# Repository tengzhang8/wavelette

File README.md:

wavelette
=========

wavelette.com

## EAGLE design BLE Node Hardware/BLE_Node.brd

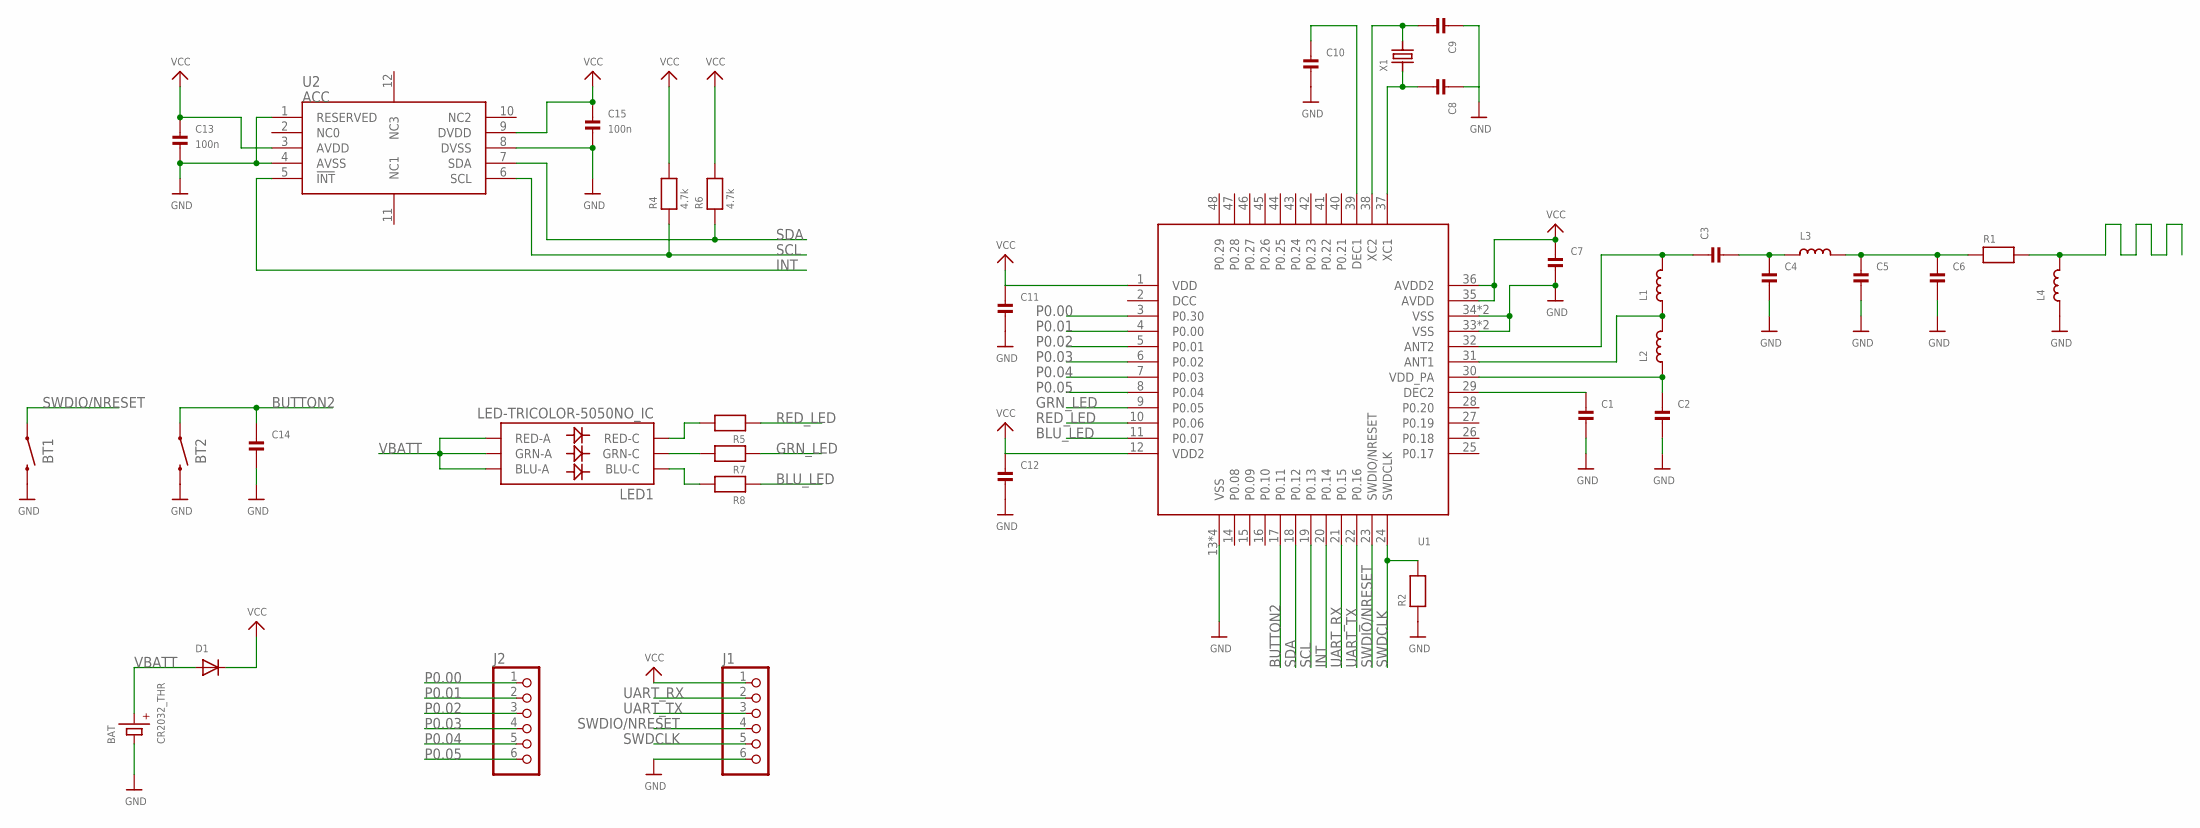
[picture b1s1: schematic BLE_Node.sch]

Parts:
BAT: CR2032_THR
BT1, BT2: TACT_SWITCH_3.5MM_6MM; TACT_SW_3.5MM_6MM
C1, C2, C3, C4, C5, C6, C7, C8, C9, C10, C11, C12, C14: NRF51_CAP_0402
C13, C15: 100n; NRF51_CAP_0402
D1: DIODESOT23_REFLOW; SOT23-R
J1, J2: HEADER-1X6ROUND; 1X06_ROUND
L1, L2, L3, L4: NRF51_IND_0402
LED1: LED-TRICOLOR-5050NO_IC; LED-TRICOLOR-5050
R1, R2, R5, R7, R8: NRF51_RES_0402
R4, R6: 4.7k; NRF51_RES_0402
U1: NRF51822_QFN48; NORDIC_QFN48
U2: ACC; DFN10
X1: TSX-3225_16MHZ; XTAL_3.2X2.5

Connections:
BLU_LED: R8.1, U1.11 (P0.07)
BUTTON2: BT2.1, C14.1, U1.17 (P0.11)
GND: BAT.5 (-), BT1.2, BT2.2, C1.2, C2.2, C4.2, C5.2, C6.2, C7.2, C8.1, C9.1, C10.2, C11.2, C12.2, C13.2, C14.2, C15.2, J1.6, L4.1, R2.1, U1.13 (VSS), U1.33 (VSS), U1.34 (VSS), U1.49 (VSS), U1.50 (VSS), U1.51 (VSS), U1.52 (VSS), U1.53 (VSS), U2.1 (RESERVED), U2.4 (AVSS), U2.8 (DVSS)
GRN_LED: R7.1, U1.9 (P0.05)
INT: U1.20 (P0.14), U2.5 (!INT)
unnamed: L1.1, L2.2, U1.31 (ANT1)
unnamed: C1.1, U1.29 (DEC2)
unnamed: C2.1, L2.1, U1.30 (VDD_PA)
unnamed: C3.1, L1.2, U1.32 (ANT2)
unnamed: C3.2, C4.1, L3.1
unnamed: C5.1, C6.1, L3.2, R1.1
unnamed: L4.2, R1.2
unnamed: C8.2, U1.37 (XC1), X1.1
unnamed: C9.2, U1.38 (XC2), X1.3 (2)
unnamed: C10.1, U1.39 (DEC1)
unnamed: LED1.5 (RED-C), R5.2
unnamed: LED1.6 (GRN-C), R7.2
unnamed: LED1.4 (BLU-C), R8.2
P0.00: J2.1, U1.3 (P0.30)
P0.01: J2.2, U1.4 (P0.00)
P0.02: J2.3, U1.5 (P0.01)
P0.03: J2.4, U1.6 (P0.02)
P0.04: J2.5, U1.7 (P0.03)
P0.05: J2.6, U1.8 (P0.04)
RED_LED: R5.1, U1.10 (P0.06)
SCL: R4.1, U1.19 (P0.13), U2.6 (SCL)
SDA: R6.1, U1.18 (P0.12), U2.7 (SDA)
SWDCLK: J1.5, R2.2, U1.24 (SWDCLK)
SWDIO/NRESET: BT1.1, J1.4, U1.23 (SWDIO/NRESET)
UART_RX: J1.2, U1.21 (P0.15)
UART_TX: J1.3, U1.22 (P0.16)
VBATT: BAT.1 (+), BAT.2 (+), BAT.3 (+), BAT.4 (+), D1.1 (A), LED1.1 (GRN-A), LED1.2 (RED-A), LED1.3 (BLU-A)
VCC: C7.1, C11.1, C12.1, C13.1, C15.1, D1.3 (C), J1.1, R4.2, R6.2, U1.1 (VDD), U1.12 (VDD2), U1.35 (AVDD), U1.36 (AVDD2), U2.3 (AVDD), U2.9 (DVDD)

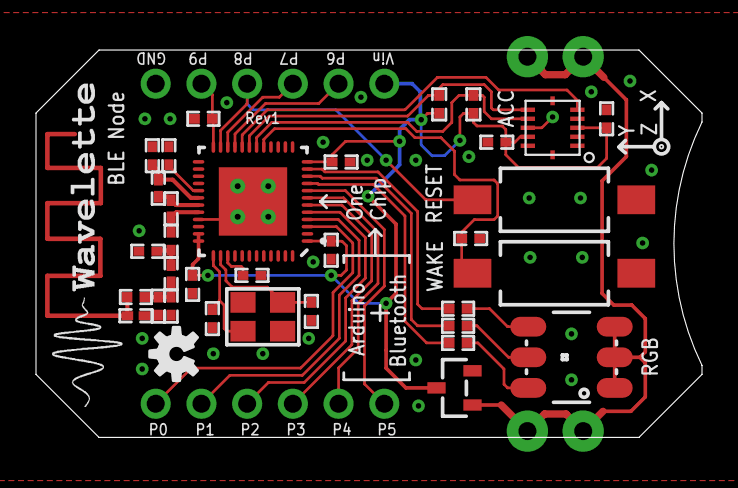
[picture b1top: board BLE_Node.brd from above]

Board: 2 copper layers, 37.0 x 21.5 mm, 38 parts (1 on the bottom side), 33 nets.

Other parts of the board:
U$9: OSHW-LOGO-S
U$11: LOGO4

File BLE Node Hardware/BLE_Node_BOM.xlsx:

Part | Description | Device | Price @100qty | Price 500 | Price 1000 |  | Source |  | 2nd Source
BAT | Battery Holder CR2032 | CR2032_THR | 0.22600000000000001 | 0.22600000000000001 | 0.20374999999999999 |  | http://www.digikey.com/product-detail/en/BAT-HLD-002-THM/BAT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 | . |  | .
BT1 | Tact Switch 3.5 x 6 | TACT_SWITCH_3.5MM_6MM | 3.3050000000000003E-2 | 3.3050000000000003E-2 | 3.3050000000000003E-2 |  | http://www.aliexpress.com/item/1000pcs-lot-Free-Shipping-SMD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 | . | http://www.digikey.com/product-detail/en/FSMSM/450-1140-ND/525812 | .
BT2 | Tact Switch 3.5 x 6 | TACT_SWITCH_3.5MM_6MM | 3.3050000000000003E-2 | 3.3050000000000003E-2 | 3.3050000000000003E-2 |  | http://www.aliexpress.com/item/1000pcs-lot-Free-Shipping-SMD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 | . | http://www.digikey.com/product-detail/en/FSMSM/450-1140-ND/525812 | .
J1 | Arduino header 6-pin | HEADER-1X6ROUND | 0.13866000000000001 | 0.13866000000000001 | 0.13866000000000001 |  | http://www.aliexpress.com/item/Free-Shipping-100-Pieces-lot-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 | . |  | .
J2 | Arduino header 6-pin | HEADER-1X6ROUND | 0.13866000000000001 | 0.13866000000000001 | 0.13866000000000001 |  | http://www.aliexpress.com/item/Free-Shipping-100-Pieces-lot-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 | . |  | .
LED1 | RGB LED | LED-TRICOLOR-5050NO_IC | 4.7919999999999997E-2 | 4.7919999999999997E-2 | 4.7919999999999997E-2 |  | http://www.aliexpress.com/item/1000-pcs-RGB-PLCC-6-5050-3-CH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 | . |  | .
U1 | nRF51822 | NRF51822_QFN48 | 2.8085 | 2.2742 | 1.9179999999999999 |  | http://www.digikey.com/product-detail/en/NRF51822-QFAB-T/149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 | . |  | .
U2 | 3-axis Accelerometer | MMA7660FC_DFN10 | 0.871 | 0.871 | 0.871 |  | http://www.digikey.com/product-detail/en/MMA7660FCT/MMA7660F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 | . |  | .
X1 | Crystal 16MHz 3225 ±15ppm | TSX-3225_16MHZ | 0.4 | 0.38 | 0.32 |  | http://www.digikey.com/product-detail/en/TSX-3225%2016.0000M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 | . |  | .
Battery | CR2032 Battery | N/A | 0.26040000000000002 | 0.25 | 0.17 |  | http://www.aliexpress.com/item/20-X-CR2032-BR2032-2032-3V-LI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 | . | http://www.aliexpress.com/item/Lithium-3V-LI-MnO2-CR2032-20-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 | .
PCB | PCB | N/A | 0.27 | 0.27 | 0.27 |  | PCBCART
C1 | 47n | Capacitor, X7R, ±10% | 6.6E-3 | 4.62E-3 | 3.5999999999999999E-3 |  | http://www.digikey.com/product-detail/en/CL05B473KO5NNNC/127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 | . |  | .
C2 | 2.2n | Capacitor, X7R, ±10% | 6.6E-3 | 4.62E-3 | 3.5999999999999999E-3 |  | http://www.digikey.com/product-detail/en/CL05B222KB5NNNC/127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 | . |  | .
C3 | 2.2p | Capacitor, NP0, ±0.1pF | 1.9800000000000002E-2 | 1.3860000000000001E-2 | 1.0800000000000001E-2 |  | http://www.digikey.com/product-detail/en/GRM1555C1H2R2BA01D/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 | . |  | .
C4 | 0.8p | Capacitor, NP0, ±5% | 5.3699999999999998E-2 | 3.7859999999999998E-2 | 3.108E-2 |  | http://www.digikey.com/product-detail/en/GRM1555C1HR80WA01D/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 | . |  | .
C5 | 1.5p | Capacitor, NP0, ±0.1pF | 1.21E-2 | 8.4799999999999997E-3 | 6.6E-3 |  | http://www.digikey.com/product-detail/en/C1005C0G1H1R5B050BA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 | . |  | .
C6 | 1.0p | Capacitor, NP0, ±0.1pF | 1.21E-2 | 8.4799999999999997E-3 | 6.6E-3 |  | http://www.digikey.com/product-detail/en/C1005C0G1H010B050BA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 | . |  | .
C7 | 1n | Capacitor, X7R, ±10% | 5.1000000000000004E-3 | 3.5799999999999998E-3 | 2.7899999999999999E-3 |  | http://www.digikey.com/product-detail/en/CL05B102KB5NCNC/127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 | . |  | .
C8 | 12p | Capacitor, NP0, ±2% | 1.9800000000000002E-2 | 1.3860000000000001E-2 | 1.0800000000000001E-2 |  | http://www.digikey.com/product-detail/en/GRM1555C1H120GA01D/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 | . |  | .
C9 | 12p | Capacitor, NP0, ±2% | 1.9800000000000002E-2 | 1.3860000000000001E-2 | 1.0800000000000001E-2 |  | http://www.digikey.com/product-detail/en/GRM1555C1H120GA01D/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 | . |  | .
C10 | 100n | NRF51_CAP_0402 | 5.4999999999999997E-3 | 3.8600000000000001E-3 | 3.0000000000000001E-3 |  | http://www.digikey.com/product-detail/en/CL05A104MP5NNNC/127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 | . |  | .
C11 | 100n | NRF51_CAP_0402 | 5.4999999999999997E-3 | 3.8600000000000001E-3 | 3.0000000000000001E-3 |  | http://www.digikey.com/product-detail/en/CL05A104MP5NNNC/127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 | . |  | .
C12 | 100n | NRF51_CAP_0402 | 5.4999999999999997E-3 | 3.8600000000000001E-3 | 3.0000000000000001E-3 |  | http://www.digikey.com/product-detail/en/CL05A104MP5NNNC/127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 | . |  | .
C13 | 100n | NRF51_CAP_0402 | 5.4999999999999997E-3 | 3.8600000000000001E-3 | 3.0000000000000001E-3 |  | http://www.digikey.com/product-detail/en/CL05A104MP5NNNC/127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 | . |  | .
C14 | 100n | NRF51_CAP_0402 | 5.4999999999999997E-3 | 3.8600000000000001E-3 | 3.0000000000000001E-3 |  | http://www.digikey.com/product-detail/en/CL05A104MP5NNNC/127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 | . |  | .
C15 | 100n | NRF51_CAP_0402 | 5.4999999999999997E-3 | 3.8600000000000001E-3 | 3.0000000000000001E-3 |  | http://www.digikey.com/product-detail/en/CL05A104MP5NNNC/127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 | . |  | .
R1 | 0R | Resistor, ±5%, 0.063W | 2E-3 | 1.2199999999999999E-3 | 8.9999999999999998E-4 |  | http://www.digikey.com/product-detail/en/RC1005J000CS/1276-3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 | . |  | .
R2 | 12k | NRF51_RES_0402 | 5.1000000000000004E-3 | 3.1199999999999999E-3 | 2.3E-3 |  | http://www.digikey.com/product-detail/en/RC1005J123CS/1276-4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 | . |  | .
R4 | 4.7k | NRF51_RES_0402 | 5.1000000000000004E-3 | 3.1199999999999999E-3 | 2.3E-3 |  | http://www.digikey.com/product-detail/en/RC1005J472CS/1276-4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 | . |  | .
R6 | 4.7k | NRF51_RES_0402 | 5.1000000000000004E-3 | 3.1199999999999999E-3 | 2.3E-3 |  | http://www.digikey.com/product-detail/en/RC1005J472CS/1276-4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 | . |  | .
R5 | 200R | NRF51_RES_0402 | 5.1000000000000004E-3 | 3.1199999999999999E-3 | 2.3E-3 |  | http://www.digikey.com/product-detail/en/RC1005J201CS/1276-4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 | . |  | .
R7 | 200R | NRF51_RES_0402 | 5.1000000000000004E-3 | 3.1199999999999999E-3 | 2.3E-3 |  | http://www.digikey.com/product-detail/en/RC1005J201CS/1276-4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 | . |  | .
R8 | 200R | NRF51_RES_0402 | 5.1000000000000004E-3 | 3.1199999999999999E-3 | 2.3E-3 |  | http://www.digikey.com/product-detail/en/RC1005J201CS/1276-4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 | . |  | .
L1 | 4.7n | Inductor, 160mA, ±0.1nH | 0.1169 | 0.1002 | 8.6840000000000001E-2 |  | http://www.digikey.com/product-detail/en/LQP15MN4N7B02D/490-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 | . |  | .
L2 | 10n | Inductor, 100mA, ±2% | 0.12989999999999999 | 0.1113 | 9.6460000000000004E-2 |  | http://www.digikey.com/product-detail/en/LQP15MN10NG02D/490-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 | . |  | .
L3 | 3.3n | Inductor, 190mA, ±0.1nH | 0.1169 | 0.1002 | 8.6840000000000001E-2 |  | http://www.digikey.com/product-detail/en/LQP15MN3N3B02D/490-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 | . |  | .
L4 | 1.8n | Inductor, 280mA, ±0.1nH | 0.1169 | 0.1002 | 8.6840000000000001E-2 |  | http://www.digikey.com/product-detail/en/LQP15MN1N8B02D/490-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 | . |  | .
D1 | Schottky Diode | DIODESOT23_REFLOW | 9.2700000000000005E-2 | 4.53E-2 | 3.09E-2 |  | http://www.digikey.com/product-detail/en/BAT54/BAT54FSCT-ND/458928 | . |  | .
 |  | Total: | 6.0217400000000003
 |  |  | 0.79449999999999998 | 0.60952000000000006 | 0.50725000000000009
 |  |  | #REF! | #REF! | #REF!
Shipping Protection
Box | Shipping Box | N/A | 0.28799999999999998 | 0.192 | 0.192 |  | http://www.ebay.com.au/itm/100-0S-SuperFlat-140x85x15mm-Larg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 | . |  | .
Padded Envelope | N/A | N/A | 0.20899999999999999 | 0.12426 | 0.12426 |  | http://www.ebay.com.au/itm/100-NEW-0B-120x180mm-Bubble-Maile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 | . |  | .
Bag | Anti-static Bag | N/A | 0.04 | 0.04 | 0.04 |  | http://www.ebay.com.au/itm/100-ESD-Pouches-Anti-Static-Shiel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 | . |  | .
 |  |  | 0.53700000000000003 | 0.35625999999999997 | 0.35625999999999997
 |  |  | #REF! | #REF! | #REF!
 |  |  | #REF! | #REF! | #REF!
Maybes:
Bag | Anti-static Bubble Bag | N/A | 0.1439 | 9.5619999999999997E-2 | 9.5619999999999997E-2 |  | http://www.aliexpress.com/item/GREAT-BULK-PRICE-100-ANTI-Sta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 | . |  | .

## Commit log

2014-10-11 Add eagle hardware design files
2014-10-13 Add initial arduino library code
    Note: Needs to be used with Arduino 1.5.2
2014-10-13 Add example program for the nordic eval kit
2014-10-14 Add bootloader main.c patch file
    Contains the diff of main.c in the nRF51 SDK v5.2, project
    nrf51822\Board\nrf6310\device_firmware_updates\bootloader
2014-11-19 Updated bootloader
    Added a bootloader specific to the PCA10001 board from the Nordic Semi
    evaluation kit. Other relevant bootloaders will be added later.

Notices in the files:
parts and their libraries:
microbuilder: This work is placed in the public domain, and may be freely used for commercial and non-commercial work with the following conditions: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
SparkFun: Licensing: CC v3.0 Share-Alike You are welcome to use this library for commercial purposes.
